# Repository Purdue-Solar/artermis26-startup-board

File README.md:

PSR Startup Board - Artemis 2027

The purpose of this board is to activate the power distro board and indicate to the power distro board which mode of operation the car should be in. There is also a forward neutral reverse switch, which goes to the steering wheel. 

The FNR switch has three states, and each line is pulled high using an internal pullup resistor in the power distro board microcontroller. This means that the logic is inverted (if a line is driven low, it is activated).

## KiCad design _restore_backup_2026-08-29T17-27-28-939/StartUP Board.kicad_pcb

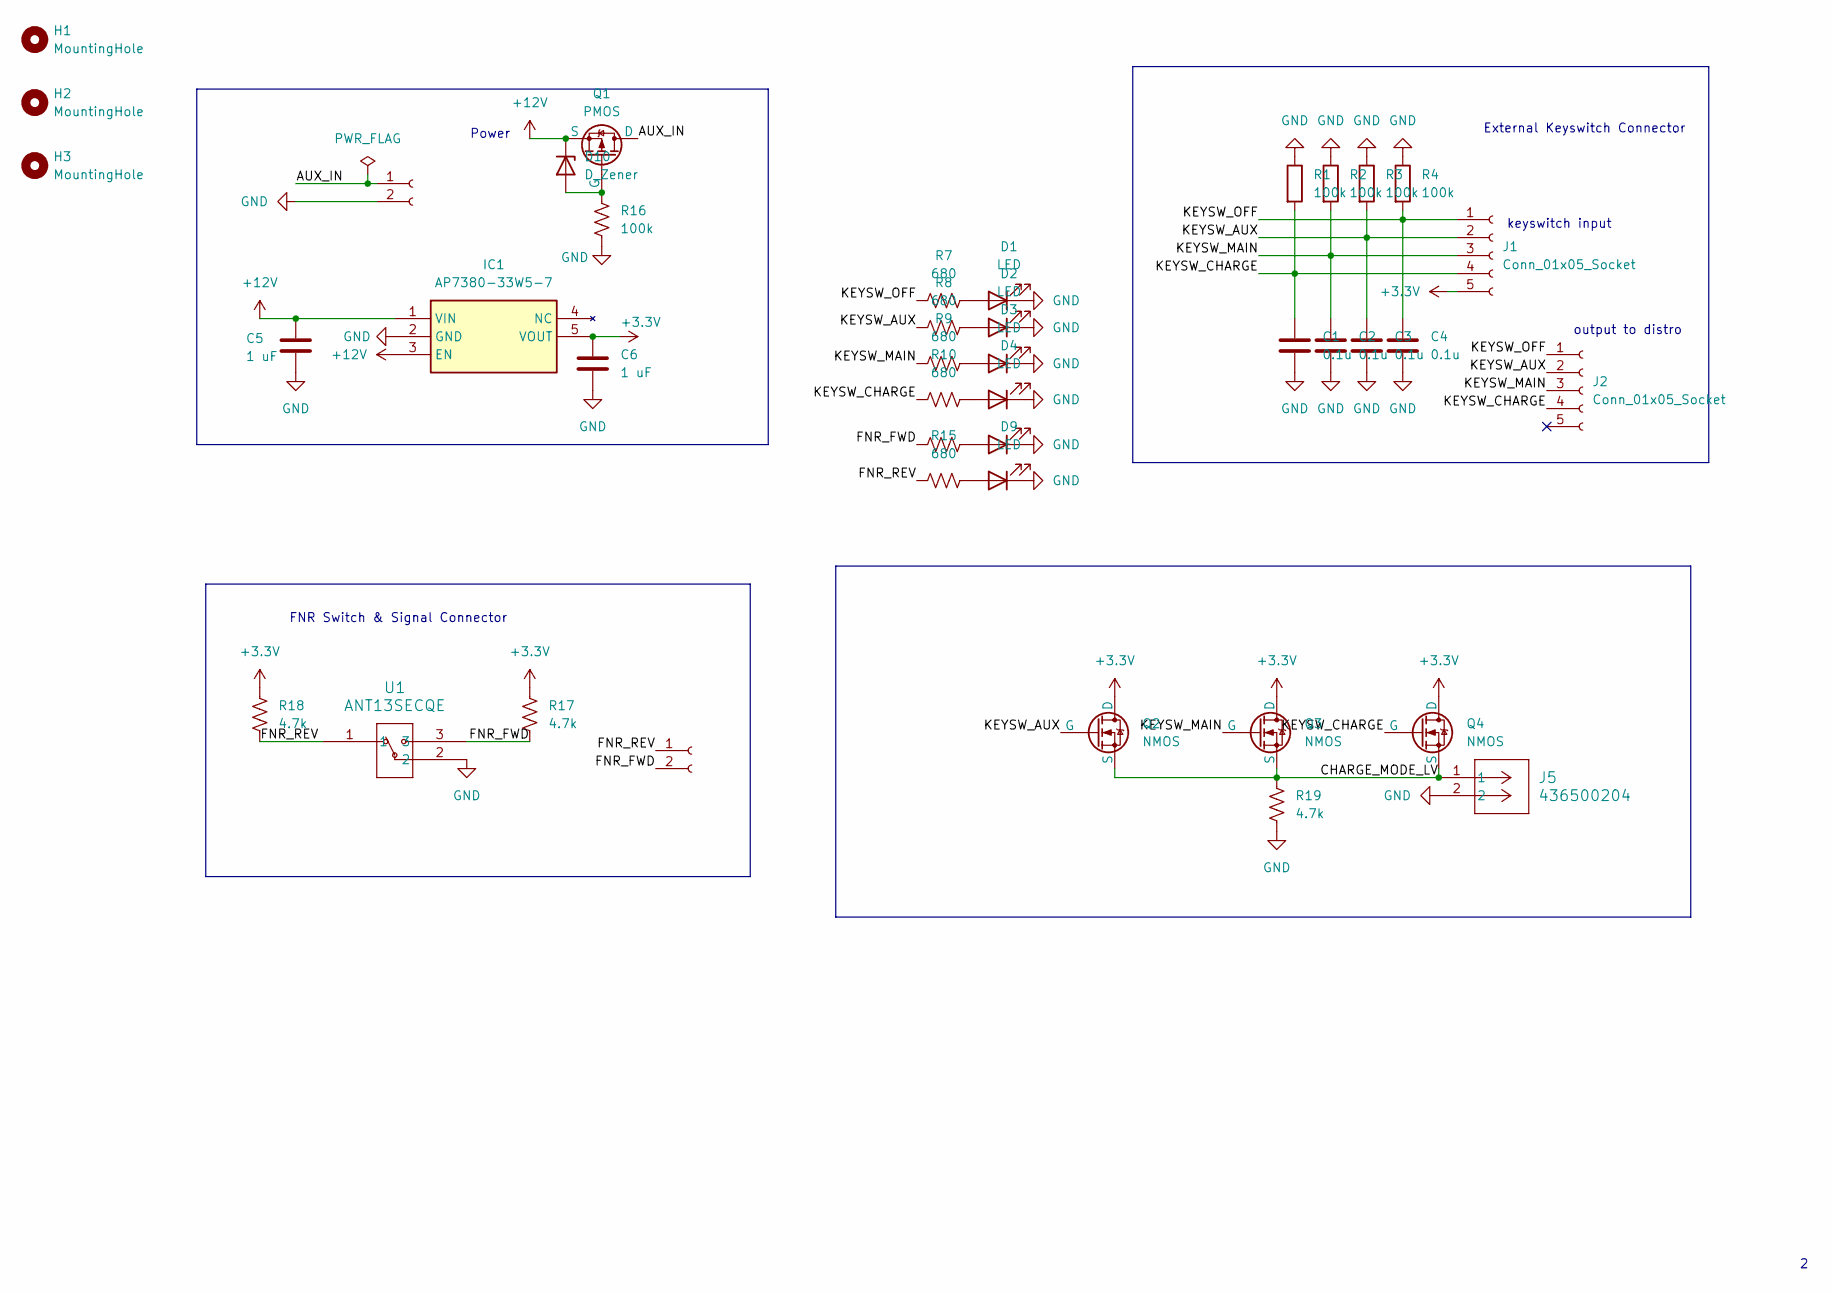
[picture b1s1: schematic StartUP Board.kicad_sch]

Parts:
C1, C2, C3, C4: 0.1u; C_0805_2012Metric
C5, C6: 1 uF; C_0805_2012Metric
D1, D2, D3, D4, D8, D9: LED; LED_0805_2012Metric
D10: D_Zener; D_0805_2012Metric
H1, H2, H3: MountingHole; MountingHole_3.2mm_M3
IC1: AP7380-33W5-7; Mouser Part Number 621-AP7380-33W5-7
J1, J2: Conn_01x05_Socket; Molex_Micro-Fit_3.0_43650-0500_1x05_P3.00mm_Horizontal
J3: Molex_Micro-Fit_3.0_43650-0200_1x02_P3.00mm_Horizontal
J4: Molex_Mega-Fit_76825-0002_2x01_P5.70mm_Horizontal
J5: 436500204; CONN_SD-43650-002_02_MOL
Q1: PMOS; TSOT-23
Q2, Q3, Q4: NMOS; TSOT-23
R1, R2, R3, R4, R16: 100k; R_0805_2012Metric
R7, R8, R9, R10, R14, R15: 680; R_0805_2012Metric
R17, R18, R19: 4.7k; R_0805_2012Metric
U1: ANT13SECQE; ANT13SEC_CRS

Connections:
+3.3V: C6.1, IC1.5 (VOUT), J1.5, Q2.1 (D), Q3.1 (D), Q4.1 (D), R17.2, R18.2
+12V: C5.1, D10.1 (K), IC1.1 (VIN), IC1.3 (EN), Q1.3 (S)
/AUX_IN: J4.1, Q1.1 (D)
/CHARGE_MODE_LV: J5.1, Q2.3 (S), Q3.3 (S), Q4.3 (S), R19.2
/FNR_FWD: J3.2, R14.1, R17.1, U1.3
/FNR_REV: J3.1, R15.1, R18.1, U1.1
/KEYSW_AUX: C3.1, J1.2, J2.2, Q2.2 (G), R3.2, R8.1
/KEYSW_CHARGE: C1.1, J1.4, J2.4, Q4.2 (G), R1.2, R10.1
/KEYSW_MAIN: C2.1, J1.3, J2.3, Q3.2 (G), R2.2, R9.1
/KEYSW_OFF: C4.1, J1.1, J2.1, R4.2, R7.1
GND: C1.2, C2.2, C3.2, C4.2, C5.2, C6.2, D1.1 (K), D2.1 (K), D3.1 (K), D4.1 (K), D8.1 (K), D9.1 (K), IC1.2 (GND), J4.2, J5.2, R1.1, R2.1, R3.1, R4.1, R16.1, R19.1, U1.2
unnamed: D1.2 (A), R7.2
unnamed: D2.2 (A), R8.2
unnamed: D3.2 (A), R9.2
unnamed: D4.2 (A), R10.2
unnamed: D8.2 (A), R14.2
unnamed: D9.2 (A), R15.2
unnamed: D10.2 (A), Q1.2 (G), R16.2

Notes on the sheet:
Power
keyswitch input
FNR Switch & Signal Connector
External Keyswitch Connector
output to distro

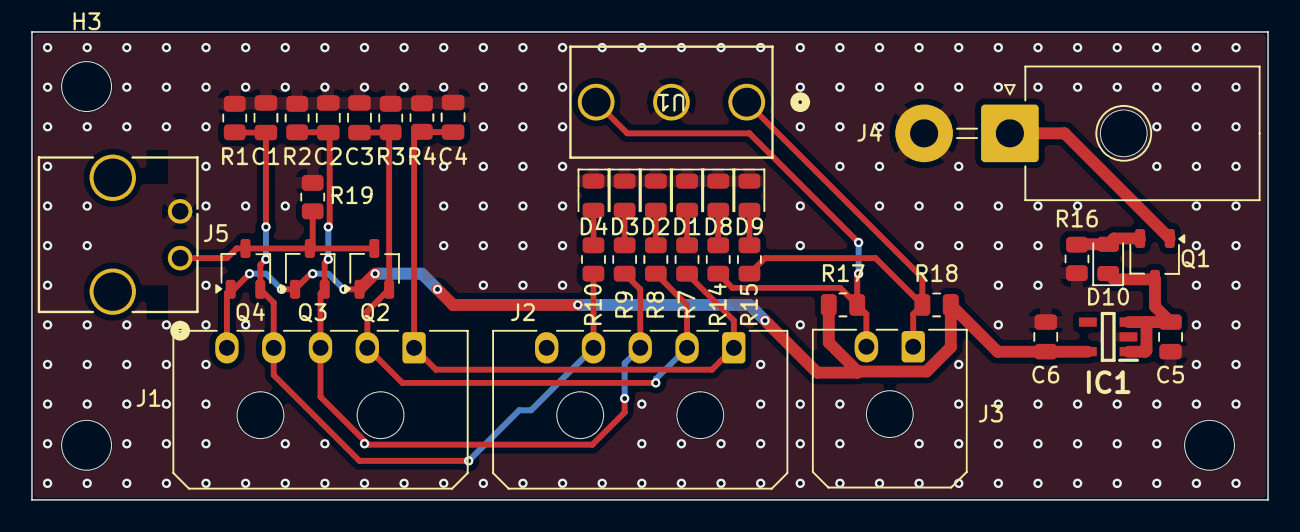
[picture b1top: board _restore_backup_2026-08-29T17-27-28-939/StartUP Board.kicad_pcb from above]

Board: 2 copper layers, 79.2 x 30.0 mm, 41 parts (0 on the bottom side), 18 nets.

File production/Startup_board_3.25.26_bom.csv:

Designator,Footprint,Quantity,Value,LCSC Part #
"C1, C2, C3, C4",0805,4,0.1u,
"C5, C6",0805,2,1 uF,
IC1,AP7380-33W5-7,1,AP7380-33W5-7,
J1,Molex_Micro-Fit_3.0_43650-0500_1x05_P3.00mm_Horizontal,1,Conn_01x05_Socket,
"J2, J3, J5",Molex_Micro-Fit_3.0_43650-0200_1x02_P3.00mm_Horizontal,3,~,
J4,Molex_Mega-Fit_76825-0002_2x01_P5.70mm_Horizontal,1,~,
"R1, R2, R3, R4, R5, R6",0805,6,100k,
U1,ANT13SEC_CRS,1,ANT13SECQE,
U2,D16-M,1,CD4049UBDR,

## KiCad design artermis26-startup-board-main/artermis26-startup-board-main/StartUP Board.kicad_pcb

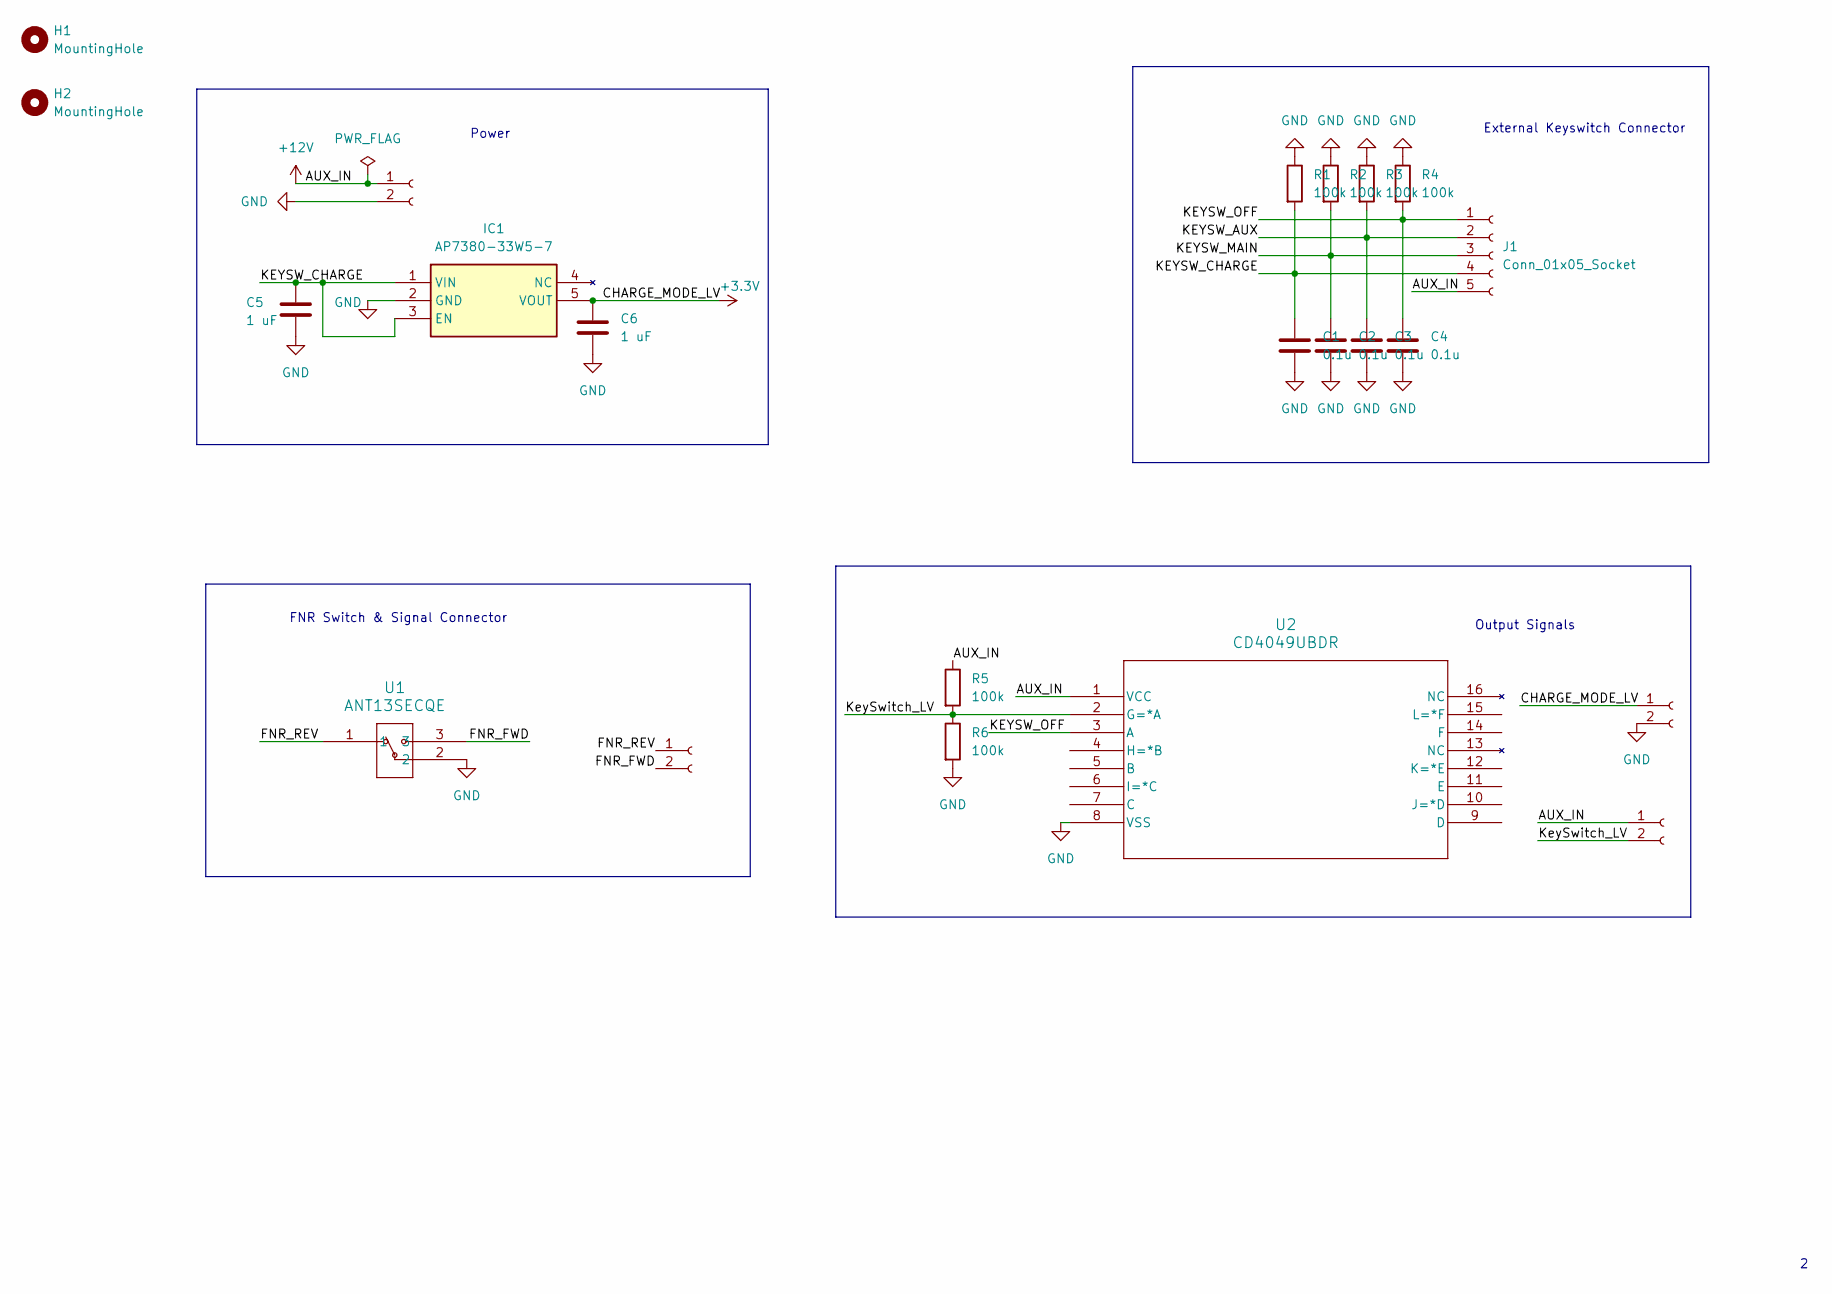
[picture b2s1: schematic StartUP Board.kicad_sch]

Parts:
C1, C2, C3, C4: 0.1u; C_0805_2012Metric
C5, C6: 1 uF; C_0805_2012Metric
H1, H2: MountingHole; MountingHole_3.2mm_M3
IC1: AP7380-33W5-7; Mouser Part Number 621-AP7380-33W5-7
J1: Conn_01x05_Socket; Molex_Micro-Fit_3.0_43650-0500_1x05_P3.00mm_Horizontal
J2, J3, J5: Molex_Micro-Fit_3.0_43650-0200_1x02_P3.00mm_Horizontal
J4: Molex_Mega-Fit_76825-0002_2x01_P5.70mm_Horizontal
R1, R2, R3, R4, R5, R6: 100k; R_0805_2012Metric
U1: ANT13SECQE; ANT13SEC_CRS
U2: CD4049UBDR; D16-M

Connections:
+3.3V: C6.1, IC1.5 (VOUT), J5.1
+12V: J1.5, J2.1, J4.1, R5.1, U2.1 (VCC)
/FNR_FWD: J3.2, U1.3
/FNR_REV: J3.1, U1.1
/KEYSW_AUX: C3.1, J1.2, R3.2
/KEYSW_CHARGE: C1.1, C5.1, IC1.1 (VIN), IC1.3 (EN), J1.4, R1.2
/KEYSW_MAIN: C2.1, J1.3, R2.2
/KEYSW_OFF: C4.1, J1.1, R4.2, U2.3 (A)
/KeySwitch_LV: J2.2, R5.2, R6.1, U2.2 (G=*A)
GND: C1.2, C2.2, C3.2, C4.2, C5.2, C6.2, IC1.2 (GND), J4.2, J5.2, R1.1, R2.1, R3.1, R4.1, R6.2, U1.2, U2.8 (VSS)

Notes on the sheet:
Power
Output Signals
FNR Switch & Signal Connector
External Keyswitch Connector

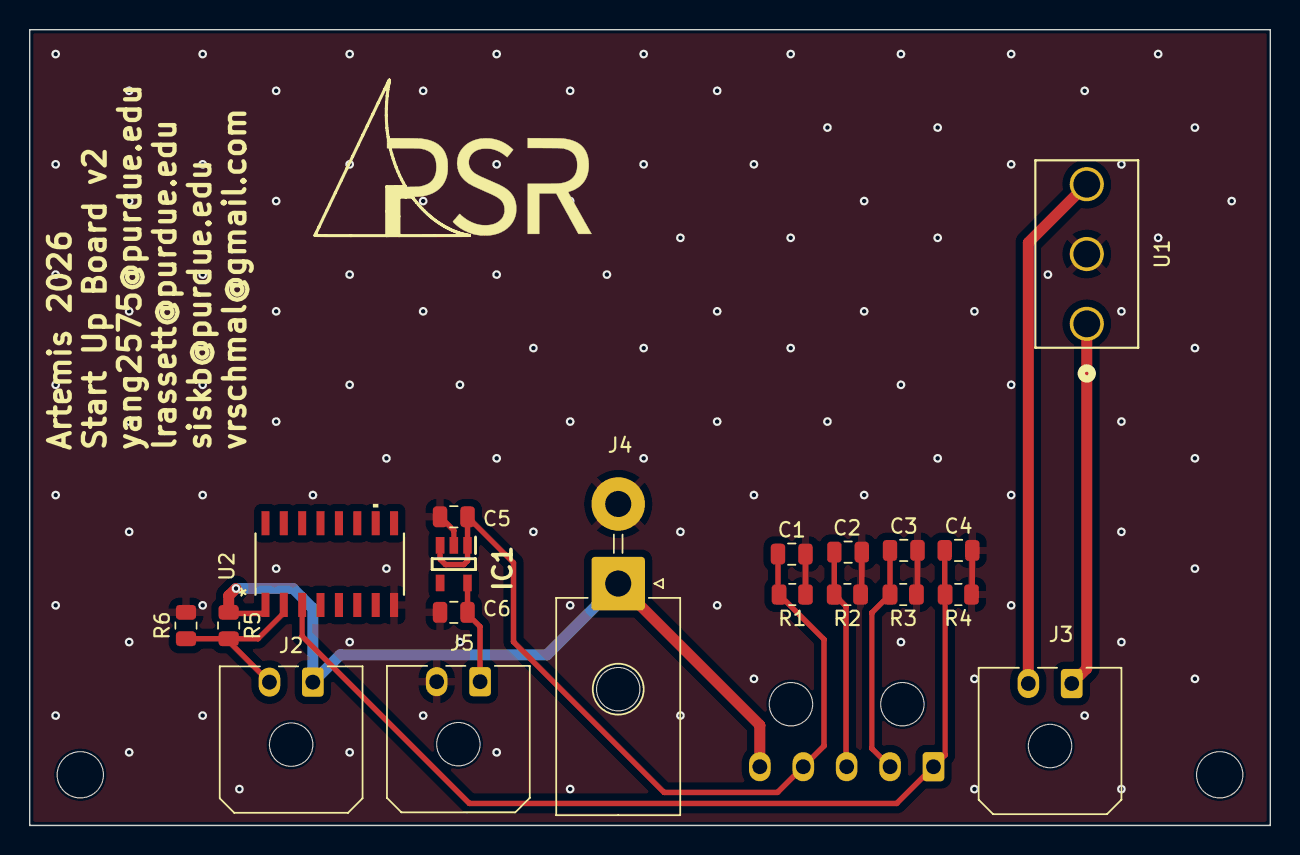
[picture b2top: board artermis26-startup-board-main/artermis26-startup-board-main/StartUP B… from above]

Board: 2 copper layers, 85.8 x 55.0 mm, 22 parts (1 on the bottom side), 10 nets.

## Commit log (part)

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2025-07-26 pcb board progress, schematic should be finalized
2025-08-01 Updated PCB layout, added mounting holes
2025-08-01 moved connectors to the bottom of the pcb, should be mostly finished
2025-08-04 finished
2026-03-07 revised start up board 3-7-26
2026-03-07 Revised start up board, hopefully done
2026-03-08 Man added
2026-04-25 upload vivian iteration of PCB
2026-04-25 add readme.md
2026-04-26 add startup image
2026-04-26 add step files
